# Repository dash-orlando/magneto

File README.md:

# MAGNETO
3D Non-Contact Position Tracking of Magnetic Field Sources

## BUILDS
Several applications of the **MAGNETO** system are been developed by our team.
Applications or adaptations of the **MAGNETO** system are referred to **Builds**:
* 4MAG
* ENCODER
* 6MAG
* [LOCAR](https://github.com/pd3d/magneto/tree/locar/Builds/LOCAR)

### Publications
Our most recent publications include:

1.  _**Odeh, M., Nichols, E. D., Fenoglietto, F. L., & Stubbs, J.** (2018). Real-Time, Non-Contact Position Tracking of Medical Devices and Surgical Tools Through the Analysis of Magnetic Field Vectors. 2018 Design of Medical Devices Conference. doi:10.1115/dmd2018-6862_

### References
The MAGNETO project was based of the following work:

1.  _Han, X., Seki, H., Kamiya, Y., and Hikizu, M. “Wearable handwriting input device using magnetic field Geomagnetism cancellation in position calculation.” Precision Engineering Vol. 33 Issue 1 (2009), pp: 37-43. DOI 10.1016/j.precisioneng.2008.03.008._

2.  _Han, X., Seki, H., Kamiya, Y., and Hikizu, M. “Wearable handwriting input device using magnetic field 2nd report: Influence of misalignment of magnet and writing plane.” Precision Engineering Vol. 34 Issue 3 (2010), pp: 425-430. DOI 10.1016/j.precisioneng.2009.12.005_

3.  _Chen, K., Lyons, K., White, S., and Patel, S. “uTrack: 3D Input Using Two Magnetic Sensors” In Proceedings of the 26th Annual ACM Symposium on User Interface Software and Technology (UIST 2013). pp: 237-244. St. Andrews, UK, October 8th-11th, 2013. DOI 10.1145/2501988.2502035_

4.  _Chen, K., Patel, S., and Keller, S. “Finexus: Tracking Precise Motions of Multiple Fingertips Using Magnetic Sensing” In Proceedings of the 2016 CHI Conference on Human Factors in Computing Systems (CHI 2016), ACM. pp: 1504-1514. San Jose, California, USA, May 7th-12th, 2016. DOI 10.1145/2858036.2858125_

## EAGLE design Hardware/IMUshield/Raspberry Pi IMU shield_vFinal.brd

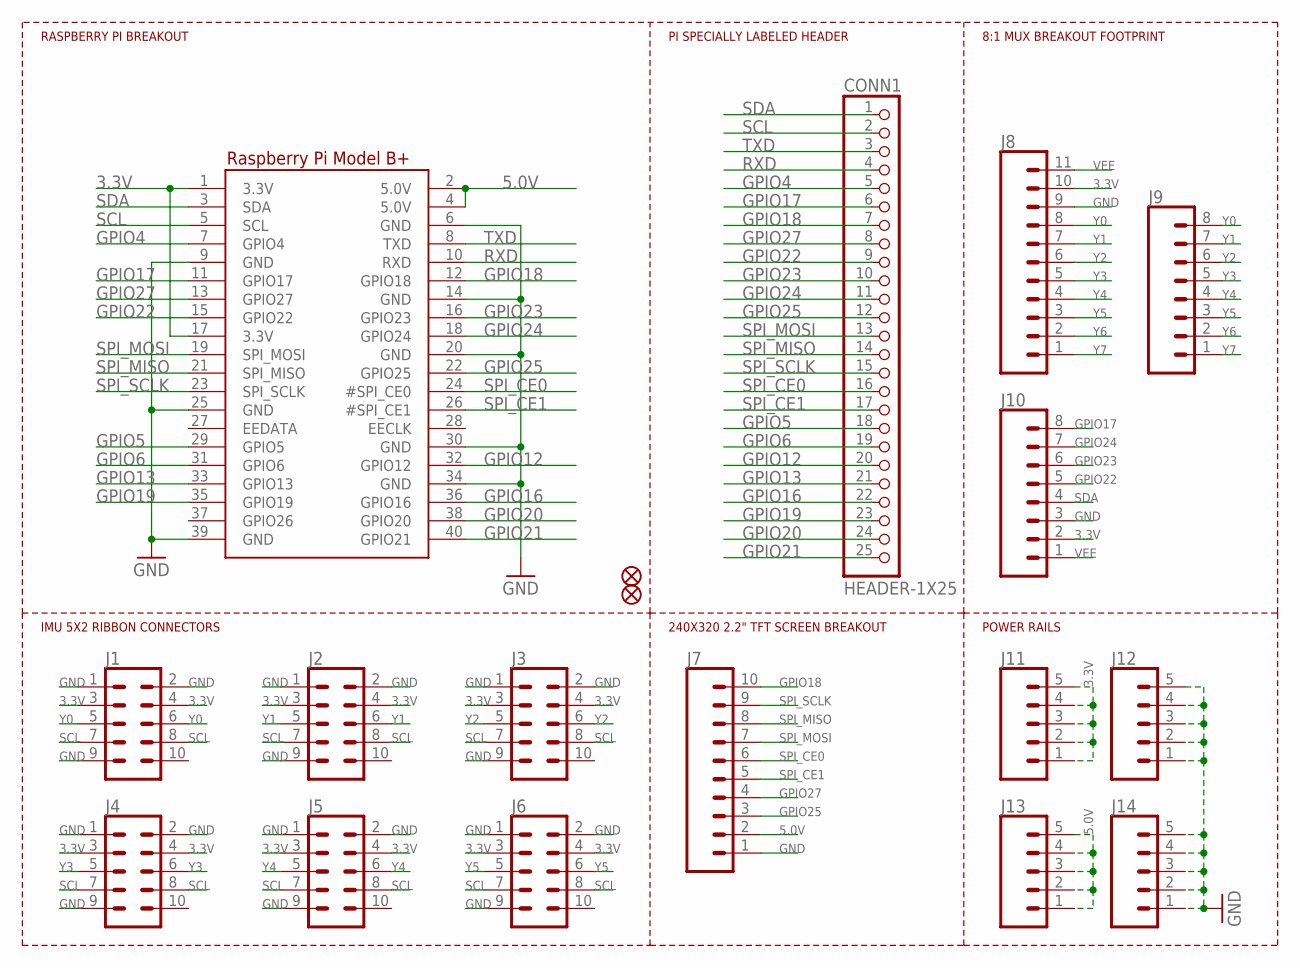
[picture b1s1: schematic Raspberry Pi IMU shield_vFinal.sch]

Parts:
CONN1: HEADER-1X25; 1X25_ROUND_70MIL
FID2, FID3: FIDUCIAL""; FIDUCIAL_1MM
J1, J2, J3, J4, J5, J6: CONN_05X2SHD; 2X5-SHROUDED
J7: CONN_10LOCK; 1X10_LOCK
J8: CONN_111X11_NO_SILK_KIT; 1X11_NO_SILK_KIT
J9, J10: CONN_08NO_SILK_FEMALE_PTH; 1X08_NO_SILK
J11, J12, J13, J14: CONN_05; 1X05
RPI1: RASPBERRYPI_BPLUS_HATNOSLOTS; PI_HAT_NOSLOTS

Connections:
3.3V: J1.3, J1.4, J2.3, J2.4, J3.3, J3.4, J4.3, J4.4, J5.3, J5.4, J6.3, J6.4, J8.10, J10.2, J11.1, J11.2, J11.3, J11.4, J11.5, RPI1.1 (3.3V), RPI1.17 (3.3V)
5.0V: J7.2, J13.1, J13.2, J13.3, J13.4, J13.5, RPI1.2 (5.0V), RPI1.4 (5.0V)
GND: J1.1, J1.2, J1.9, J2.1, J2.2, J2.9, J3.1, J3.2, J3.9, J4.1, J4.2, J4.9, J5.1, J5.2, J5.9, J6.1, J6.2, J6.9, J7.1, J8.9, J10.3, J12.1, J12.2, J12.3, J12.4, J12.5, J14.1, J14.2, J14.3, J14.4, J14.5, RPI1.6 (GND), RPI1.9 (GND), RPI1.14 (GND), RPI1.20 (GND), RPI1.25 (GND), RPI1.30 (GND), RPI1.34 (GND), RPI1.39 (GND)
GPIO4: CONN1.5, RPI1.7 (GPIO4)
GPIO5: CONN1.18, RPI1.29 (GPIO5)
GPIO6: CONN1.19, RPI1.31 (GPIO6)
GPIO12: CONN1.20, RPI1.32 (GPIO12)
GPIO13: CONN1.21, RPI1.33 (GPIO13)
GPIO16: CONN1.22, RPI1.36 (GPIO16)
GPIO17: CONN1.6, J10.8, RPI1.11 (GPIO17)
GPIO18: CONN1.7, J7.10, RPI1.12 (GPIO18)
GPIO19: CONN1.23, RPI1.35 (GPIO19)
GPIO20: CONN1.24, RPI1.38 (GPIO20)
GPIO21: CONN1.25, RPI1.40 (GPIO21)
GPIO22: CONN1.9, J10.5, RPI1.15 (GPIO22)
GPIO23: CONN1.10, J10.6, RPI1.16 (GPIO23)
GPIO24: CONN1.11, J10.7, RPI1.18 (GPIO24)
GPIO25: CONN1.12, J7.3, RPI1.22 (GPIO25)
GPIO27: CONN1.8, J7.4, RPI1.13 (GPIO27)
RXD: CONN1.4, RPI1.10 (RXD)
SCL: CONN1.2, J1.7, J1.8, J2.7, J2.8, J3.7, J3.8, J4.7, J4.8, J5.7, J5.8, J6.7, J6.8, RPI1.5 (SCL)
SDA: CONN1.1, J10.4, RPI1.3 (SDA)
SPI_CE0: CONN1.16, J7.6, RPI1.24 (#SPI_CE0)
SPI_CE1: CONN1.17, J7.5, RPI1.26 (#SPI_CE1)
SPI_MISO: CONN1.14, J7.8, RPI1.21 (SPI_MISO)
SPI_MOSI: CONN1.13, J7.7, RPI1.19 (SPI_MOSI)
SPI_SCLK: CONN1.15, J7.9, RPI1.23 (SPI_SCLK)
TXD: CONN1.3, RPI1.8 (TXD)
VEE: J8.11, J10.1
Y0: J1.5, J1.6, J8.8, J9.8
Y1: J2.5, J2.6, J8.7, J9.7
Y2: J3.5, J3.6, J8.6, J9.6
Y3: J4.5, J4.6, J8.5, J9.5
Y4: J5.5, J5.6, J8.4, J9.4
Y5: J6.5, J6.6, J8.3, J9.3
Y6: J8.2, J9.2
Y7: J8.1, J9.1

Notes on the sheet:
IMU 5X2 RIBBON CONNECTORS
240X320 2.2" TFT SCREEN BREAKOUT
RASPBERRY PI BREAKOUT
PI SPECIALLY LABELED HEADER
8:1 MUX BREAKOUT FOOTPRINT
POWER RAILS

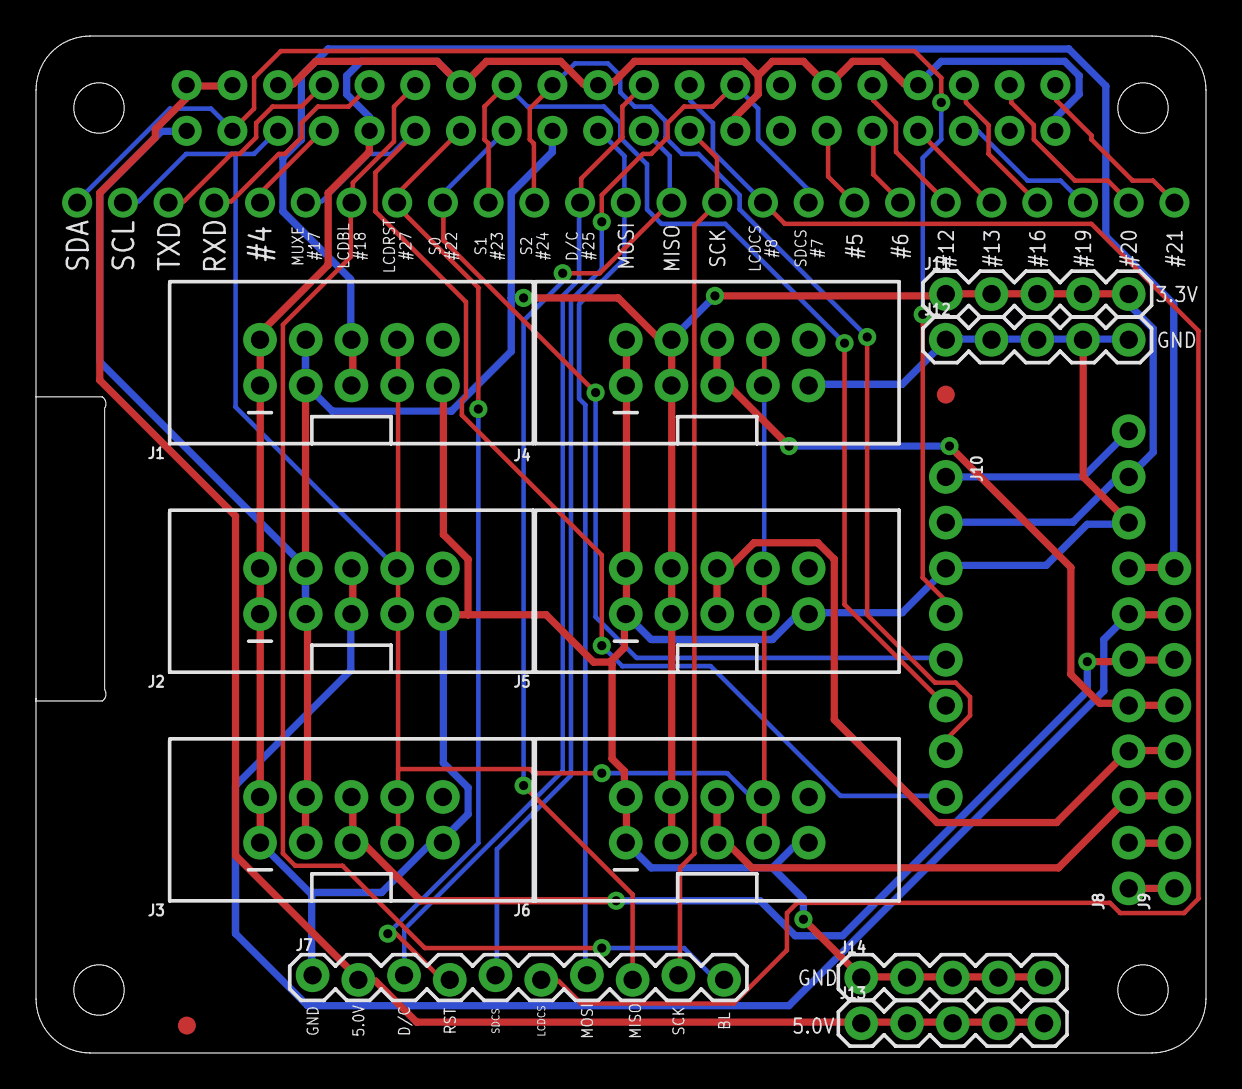
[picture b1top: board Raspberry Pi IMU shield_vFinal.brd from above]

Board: 2 copper layers, 65.0 x 56.5 mm, 18 parts (0 on the bottom side), 37 nets.

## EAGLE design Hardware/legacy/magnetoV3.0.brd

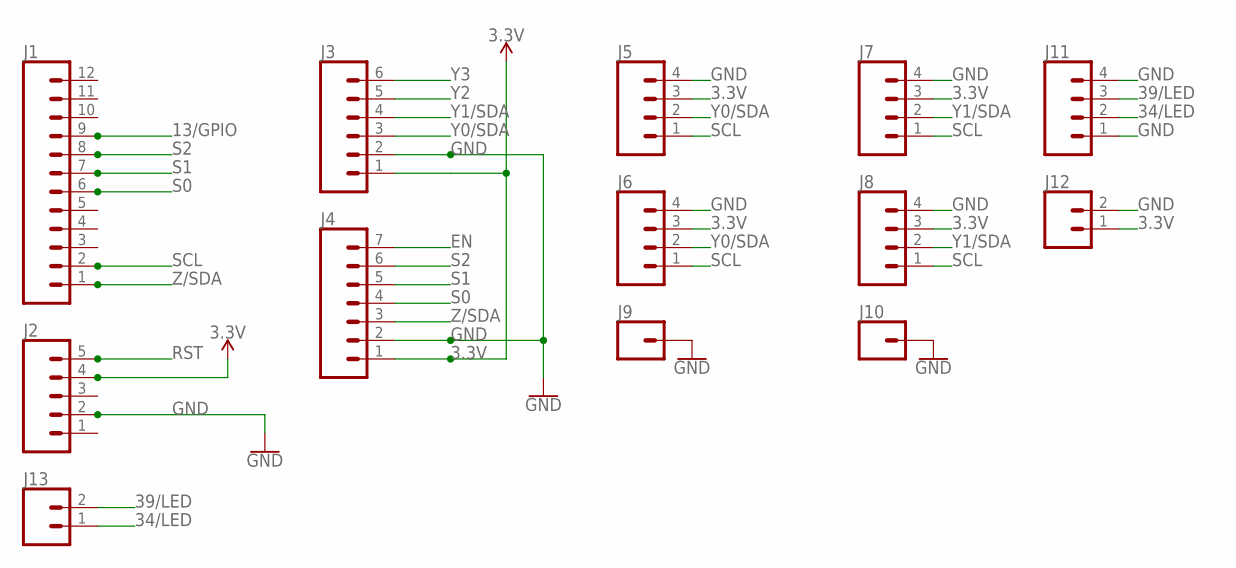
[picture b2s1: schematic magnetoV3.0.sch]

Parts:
J1: CONN_12; 1X12
J2: CONN_05; 1X05
J3: CONN_06SILK_FEMALE_PTH; 1X06
J4: CONN_07; 1X07
J5, J6, J7, J8, J11: CONN_04; 1X04
J9, J10: CONN_01; 1X01
J12, J13: CONN_02; 1X02

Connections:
3.3V: J2.4, J3.1, J4.1, J5.3, J6.3, J7.3, J8.3, J12.1
13/GPIO: J1.9
34/LED: J11.2, J13.1
39/LED: J11.3, J13.2
EN: J4.7
GND: J2.2, J3.2, J4.2, J5.4, J6.4, J7.4, J8.4, J9.1, J10.1, J11.1, J11.4, J12.2
RST: J2.5
S0: J1.6, J4.4
S1: J1.7, J4.5
S2: J1.8, J4.6
SCL: J1.2, J5.1, J6.1, J7.1, J8.1
Y0/SDA: J3.3, J5.2, J6.2
Y1/SDA: J3.4, J7.2, J8.2
Y2: J3.5
Y3: J3.6
Z/SDA: J1.1, J4.3

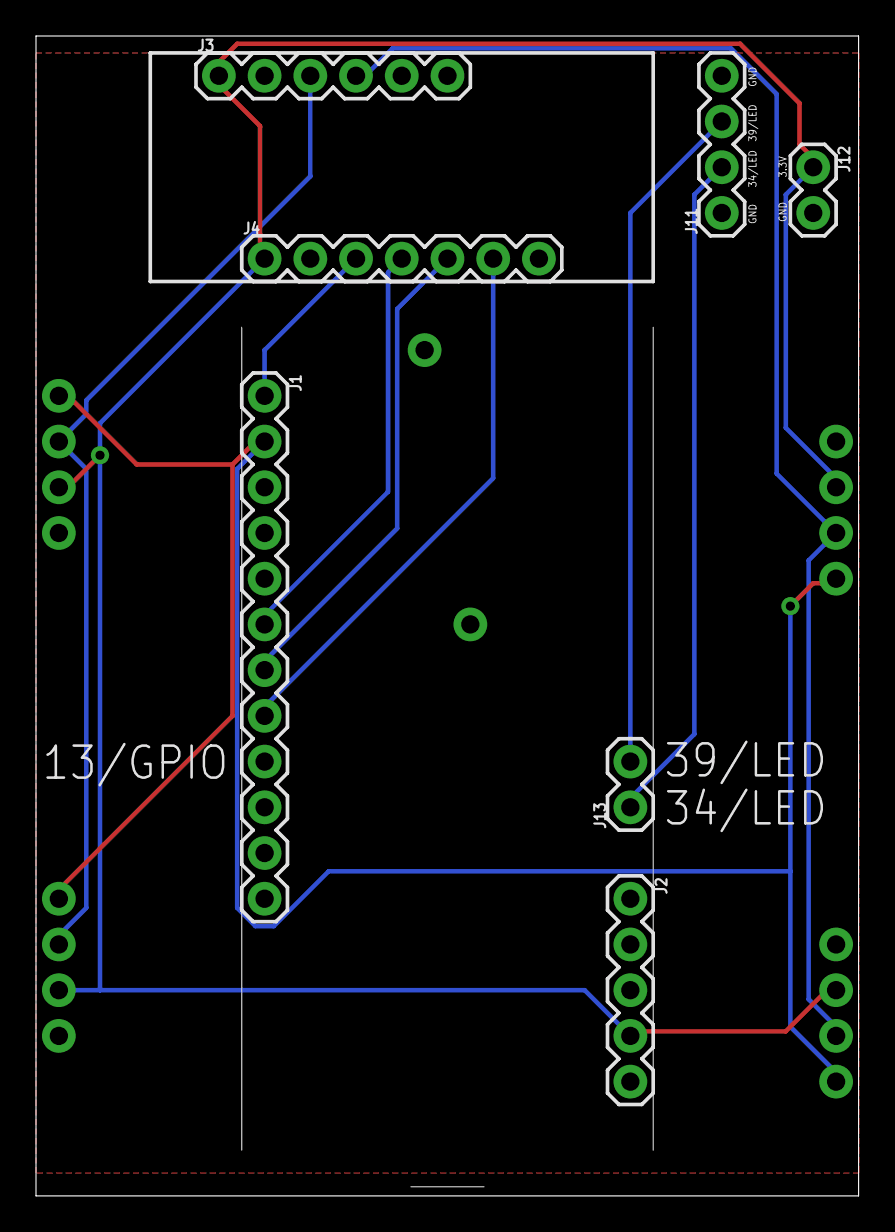
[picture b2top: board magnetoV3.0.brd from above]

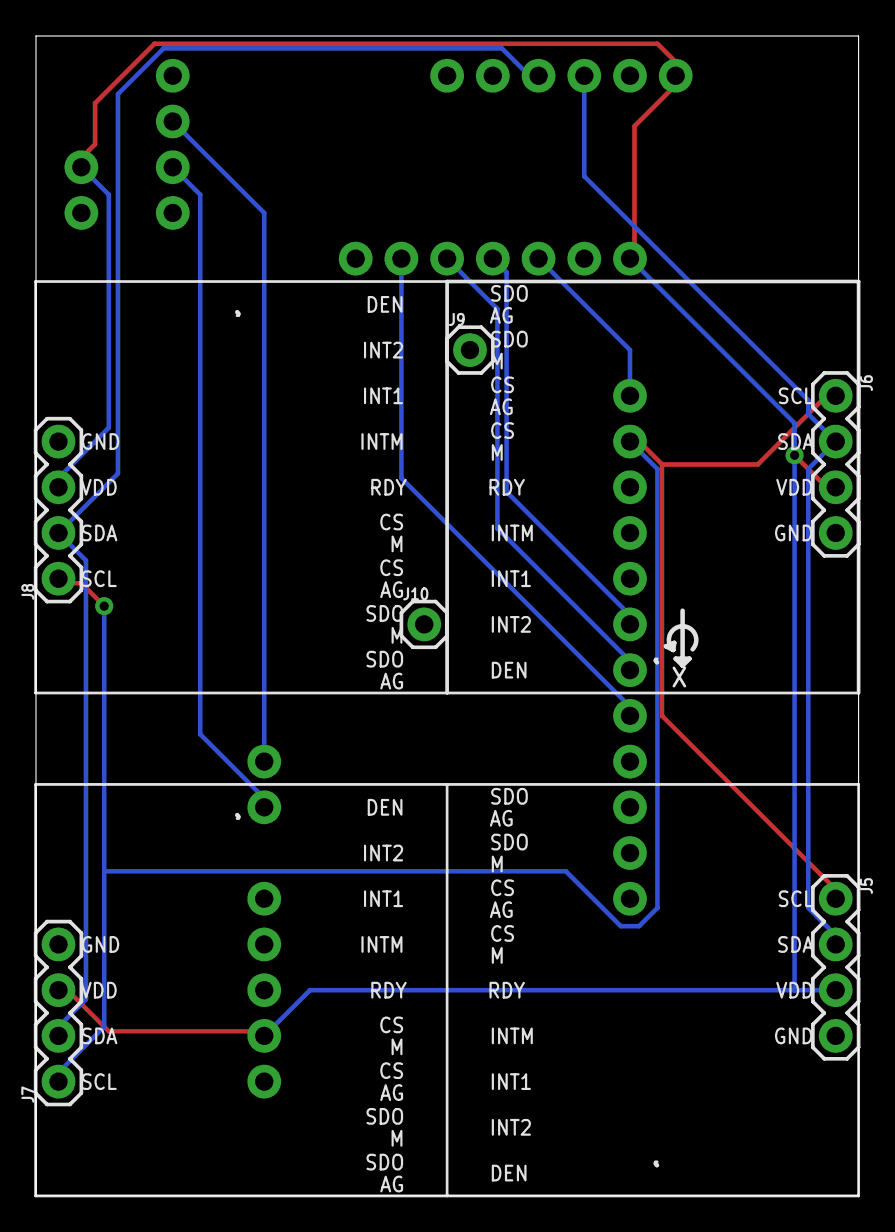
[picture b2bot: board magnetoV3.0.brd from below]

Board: 2 copper layers, 45.7 x 64.4 mm, 13 parts (6 on the bottom side), 11 nets.

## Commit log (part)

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2018-06-28 Initial arduino code
2018-06-28 Python side
2018-07-09 Fritzing-style PCB. Next iteration PCB, in progress.
2018-07-17 MQTT + stethoscope now work together
2018-07-17 Update program info
2018-07-17 Fix argument passed to argsort() in the LHS() function definition
2018-07-19 1- Move to MQTT 2- Store calibration offsets in EEPROM 3- No need to perform a hard-reset on failure
2018-07-19 Make EEPROM_write() faster, better, strongergit add .!
2018-09-10 Port original work from Stethoscope repo
2018-09-14 Created a directory for sensor libraries to be referenced or copied into the working Arduino scripts
2018-09-17 Created a directory called "builds," were entire prototypes will be consolidated and documented
2018-09-17 The latest build needed a switch in digital pins due to a hardware malfunction of the arduino in use. The reference pins should be 10, 9, and 8
2018-09-17 Added the 3D tracking python program for the 6MAG build
2018-09-17 Began working on a bash script that installs all required packages for the proper operation of the build/prototype.
2018-09-18 Added the missing usb protocol python script/module
2018-09-18 Modified the python scripts to work with a linux-based computer or control system. In our case, a chromebook running the GalliumOS linux distribution.
2018-09-24 Added different versions of the scripts for different versions of python. Later, only one version will exist.
2018-09-24 Fixed the 'queue' call issue of python3
2018-09-24 Added fixes to
2018-09-24 Minor changes to adapt to the python 3 version.
2018-09-24 Re-structure directories
2018-09-25 Created a branch and a python script to generate a gcode that forces a 3D printer to follow a specific path
2018-09-25 Generated several helix shape functions for path generation
2018-09-25 Successfully created a script that can write a gcode file. This needs to be translated into a full motion next.
2018-09-26 Completed and tested function over octoprint. The process works like a charm.
2018-09-27 Added the LAPARO directory to the Builds folder.
2018-09-28 Initial draft of Python code
2018-10-08 Commit Python port from AugmentedStethoscope repo
2018-10-09 Added python implementation to the builds directory
2018-10-09 Automate installation of dependencies on Windows
2018-10-09 Hi, I am PIP. I will not install your packages unless they have a certain name. I am racist
2018-10-11 Bagen developing a random generation gcode
2018-10-11 Corrected number of sensors and data array to be more flexible
2018-10-11 Created a 4MAG directory within the builds folder. 4-sensor-arrays are planned as prototypes.
2018-10-11 Began modifying the script to use different size arrays.
2018-10-12 Modified the getData() function to construct an extensible dictionary that replaces the individual B/H functions per sensor.
2018-10-12 Eliminated unnecessary comments
2018-10-12 Upgraded the calculations of the norms to be expandible. Next will be the function bubblesort.
2018-10-12 Better comment code + typo fixes
2018-10-12 Clean up python code
2018-10-12 Fix multiplexer not switching
2018-10-12 Re-instated a working section of the code
2018-10-15 Determine direction and number of revolutions
2018-10-16 Move to polar for rotation calculations
2018-10-22 Initial (INCOMPLETE) port of Python code to C
2018-10-24 Clean up + define find_norm_max() function
2018-10-24 fix find_max_norm(), add bubbleSort(), dynamically create required equations in system_of_eqns()
2018-10-25 Write to logfile
2018-10-26 Saved the latest version of the tracking code for the laparoscopic trainer. Also created a directory for legacy versions.
2018-10-26 Upted the usb communication protocol to the latest version
2018-10-26 Added various time-stamps to track overall program time.
2018-10-26 Data collection
2018-10-27 Added a script for data plotting and analytics
2018-10-27 Began adding statistics to the plotting script
2018-10-29 Added comments
2018-10-29 Added plotting for the error with actual position.
2018-10-31 Made some modifications to the motion scripts
2018-10-31 Created a branch specific to the work on the laparoscopic trainer. Updated the data plotting script for plane error visualization.
2018-11-01 Completed a working random walk with intervals defined in milliseconds
2018-11-01 Added the enable/disable steppers feature in the motion random walk code
2018-11-01 Updated latest version of the python script.
2018-11-01 Made minor changes to the plotting file for the laparoscopic simulator data
2018-11-02 Beta stuff
2018-11-05 Completed and tested a random walk gcode generator process for the evaluation of the magnetic tracking method.
2018-11-05 Removed useless script
2018-11-05 Tested the random walk code a little further and realized that the current version continues on a random path which could, if unlucky/lucky enough, past input limits. The next version will support re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
2018-11-06 Created and tested a version of the center random walk gocde generation process featuring retraction. Retraction consists on the return of the magnet holder to the center/origin of the printer (start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
2018-11-06 Finalize random motion script and created some test gcode files
2018-11-19 Began working on the daisypair prototype of the PC-board/breakout
2018-11-19 Tested ground fill
2018-11-19 Finihsed the daisypair design/model
2018-11-19 Updated BOM
2018-11-19 Finished the daisychain module design
2018-11-19 Saved latest changes to the daisychain module
2018-11-20 Completed the extra-small version of the IMU hubs for the daisy chain prototype.
2018-11-20 Corrected missing SCL connection on the extra small version of the IMU modules
2018-11-20 Currently working on the pi wing/hat adapter for the multiplexing.
2018-11-20 Added thin wire connections to the Locar PCB design
2018-11-20 Exported fabrication files for the pi hub PCB
2018-11-20 Updated.
2018-11-21 Began working on a version of the IMU board that has THT LEDs for signaling data line number and, thus, device pair.
2018-11-21 Created a legacy folder and placed obsolete or old versions of the daisychain boards
2018-11-21 Finished pi wing hub project, added final features and exported manufacturing files.
2018-12-03 MQTT+stethoscope demo
2018-12-14 Created a working BOM for LOCAR
2018-12-20 Re-structure directories to refer to the LOCAR prototype and the daisyhub design
2018-12-20 Created a new version of the daisyhub design. Removed the LEDs and moved the SDA solder jumpers to the bottom of the board.
2018-12-20 Began working on a version of the daisyhub design that allows for up to 14 pairs of sensors.
2019-02-21 Added README file to the repo branch
2019-02-21 Update README.md
    Added note on development branch
2019-02-21 Added the components of the python and C-based tracking programs onto the LOCAR repo
2019-02-21 Restructure the windows directory
2019-02-21 Updated BOMs
2019-02-28 Added the power supply PCB designed by MB
2019-02-28 Built the latest version of the C implementation for testing on the Pi 3A.
2019-02-28 Eliminated an unnecessary folder/file.
2019-02-28 Eliminated IMU-specific files placed in the folder prior to properly learning how to build the application.
2019-02-28 Finished the automated build bash file for the magneto program. Will continue to work on further developing its clean-up features.
2019-02-28 Formatted automated bash file to provide feedback to the user.
2019-02-28 Added a termination message and tested execution.
2019-02-28 Update README.md
    Added reference publications
2019-02-28 Update README.md
    Added a description to the "builds". Will add links shortly.
2019-02-28 Rename magneto_pi_c_install.md to README.md
    changed the filename to be readable immediately
2019-03-01 Rename LOCAR.md to README.md
    Changed filename to make content visible directly
2019-03-01 Began adapting the end-effector calculation functionality to the magneto application. Later, the wntire functionality should be flagged.
2019-03-04 Continued developing the end_effector.h function for the LOCAr application. Currently integrated all the calculations.
2019-03-04 Modify debug flag to include option specific to the end-effector functionality.
2019-03-04 Removed and tested the definition debug statement from the end effector function. There should only be one call to this flag from the magneto script.
2019-03-05 Working on the debug flag, ensuring other functions are not printing due to the new debug definitions.
2019-03-05 Added time as an input to the end-effector function to measure, print, store execution time.
2019-03-05 Update README.md
    Added background section and reference
2019-03-05 Update README.md
    Added most recent publication
2019-03-05 Update README.md
    Added website link for the project
2019-03-05 Update README.md
    Added the link to the C implementation instructions
2019-03-05 Update README.md
    Added line separators
2019-03-06 Update README.md
    Started populating the installation instructions of the C implementation of magneto and locar
2019-03-06 Update README.md
    Completed basic setup instruction
2019-03-06 Update README.md
    Began working on an extended section to describe the build.sh file and its operation.
2019-03-06 Modified the build.sh to run including the clean-up calls of make on a brand new pi.
2019-03-06 Update README.md
    Added the I2C communication enable step
2019-03-06 Update README.md
    Changed formatting on the troubleshooting scheme
2019-03-06 Update README.md
    Added the execution section
2019-03-12 Added some changes
2019-03-12 Created the directories associated with the programs specific to the functionality of the Raspberry Pi acting as the control module of LOCAR.
2019-03-12 Realized that the wifi setup bash files should actually go into the array directory. Cleared the control folder and left a note instructing the future content.
2019-03-12 Added a bash script to simplify the process of listing leased iP address (connected Pis).
2019-03-12 Updated the guide with the latest
2019-03-12 Create pibridge_manual_install
    Created a guide for the manual installation of an ethernet-wifi bridge for the pi
2019-03-12 Update README.md
    Formatting
2019-04-08 added python3 scripts to show video stream through opencv and light led's
2019-04-08 Create README.md
    create readme for scripts
2019-04-08 Update README.md
    added README for stream and lighting script
2019-04-08 changed script to run properly with arguments and python3
2019-04-08 Rename documentation.txt to Setup.md
    setup for raspberry pi to work with picamera, opencv, and neopixel light ring.
2019-04-09 Create README.md
    Created readme file for the proper installation and execution of the control pi of the LOCAR system
2019-04-09 Update README.md
    Began working on the installation instructions
2019-04-09 Rename pibridge_manual_install.md to README_pibridge_install.md
    Changed the name of the file
2019-04-09 Rename pinat_manual_install.md to README_pinat_install.md
    Changed file name
2019-04-09 Update README_pinat_install.md
    Updated title
2019-04-09 Update README_pinat_install.md
    Started updating the installation guide
2019-04-09 Update README_pinat_install.md
    Formatting guide
2019-04-09 Corrected the initial position values of the sensor array elements to be LOCAR (6MAG) specific.
2019-04-10 reset paths and added bash start steam ecexutable
2019-04-10 changed start bash script for clarity
2019-04-10 updated bash file
2019-04-10 added ssh shutdown executables
2019-04-10 added self pi shutdown
2019-04-11 Last minute modifications to ensure LOCAR prototype works.

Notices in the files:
parts and their libraries:
microbuilder: This work is placed in the public domain, and may be freely used for commercial and non-commercial work with the following conditions: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
SparkFun-Connectors: Licensing: Creative Commons ShareAlike 4.0 International - https://creativecommons.org/licenses/by-sa/4.0
